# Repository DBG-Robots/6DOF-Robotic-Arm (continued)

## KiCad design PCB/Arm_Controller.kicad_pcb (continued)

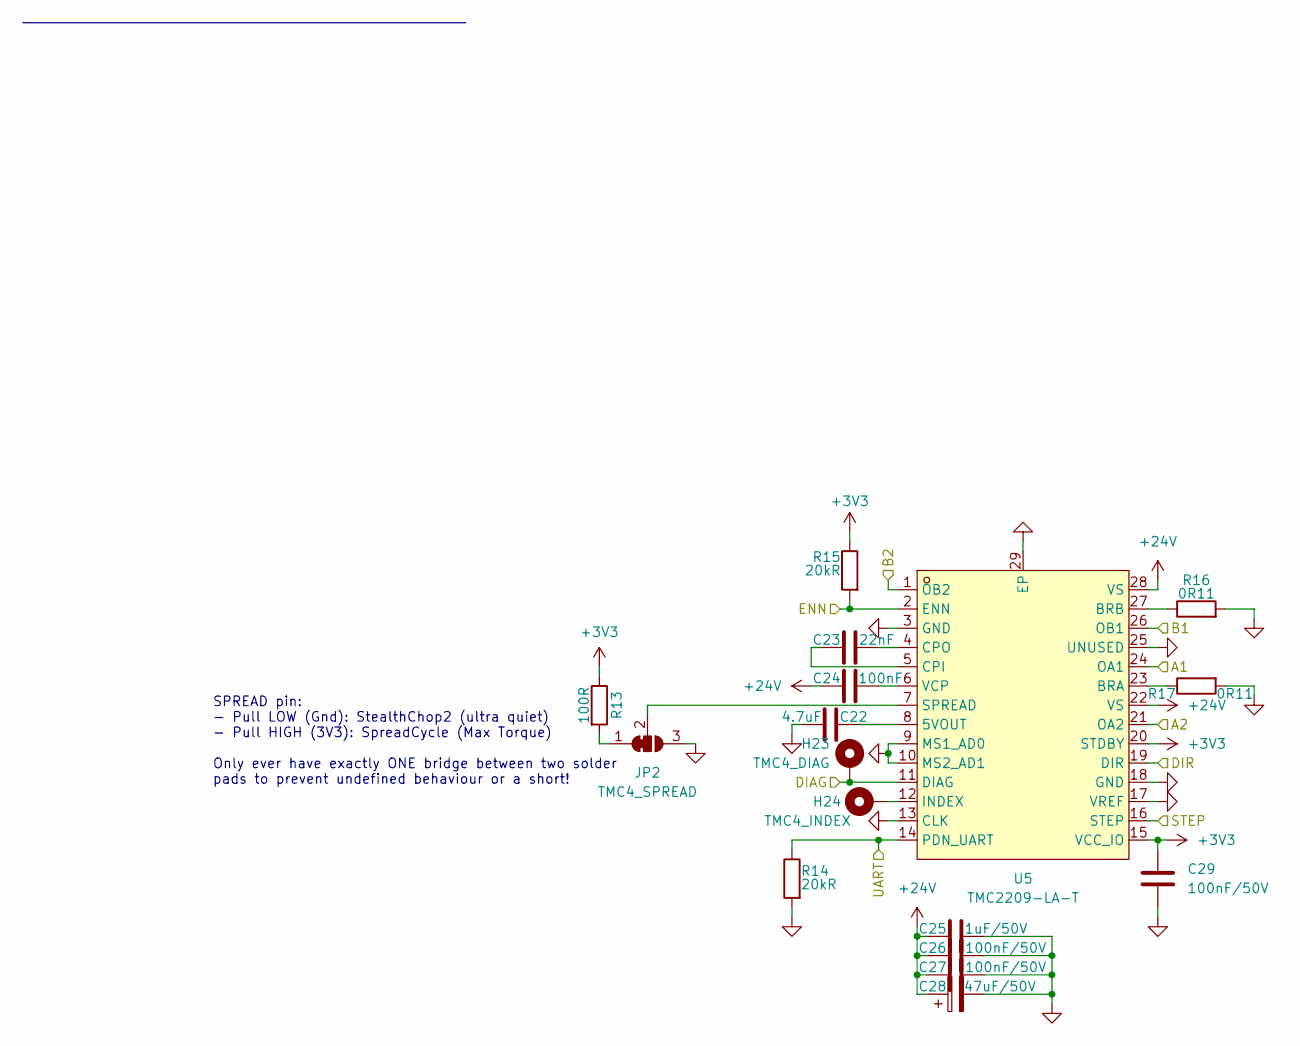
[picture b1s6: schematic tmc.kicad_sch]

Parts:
C22: 4.7uF; C_0805_2012Metric
C23: 22nF; C_0402_1005Metric
C24: 100nF; C_0402_1005Metric
C25: 1uF/50V; C_0603_1608Metric
C26, C27, C29: 100nF/50V; C_0402_1005Metric
C28: 47uF/50V; CP_Elec_8x10.5
H23: TMC4_DIAG; TestPoint_Pad_D1.0mm
H24: TMC4_INDEX; TestPoint_Pad_D1.0mm
JP2: TMC4_SPREAD; SolderJumper-3_P1.3mm_Bridged2Bar12_RoundedPad1.0x1.5mm
R13: 100R; R_0402_1005Metric
R14, R15: 20kR; R_0402_1005Metric
R16, R17: 0R11; R_1206_3216Metric
U5: TMC2209-LA-T; QFN-28_L5.0-W5.0-P0.50-BL-EP; MPN TMC2209-LA-T; LCSC Part C2150710

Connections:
+3V3: C29.1, R13.1, R15.1, U5.15 (VCC_IO), U5.20 (STDBY); also elsewhere on the board
+24V: C24.1, C25.1, C26.1, C27.1, C28.1, U5.22 (VS), U5.28 (VS); also elsewhere on the board
GND: C22.1, C25.2, C26.2, C27.2, C28.2, C29.2, JP2.3 (B), R14.2, R16.2, R17.2, U5.3 (GND), U5.9 (MS1_AD0), U5.10 (MS2_AD1), U5.13 (CLK), U5.17 (VREF), U5.18 (GND), U5.25 (UNUSED), U5.29 (EP); also elsewhere on the board
unnamed: JP2.1 (A), R13.2
unnamed: JP2.2 (C), U5.7 (SPREAD)
unnamed: C22.2, U5.8 (5VOUT)
unnamed: R17.1, U5.23 (BRA)
unnamed: R16.1, U5.27 (BRB)
unnamed: C23.1, U5.5 (CPI)
unnamed: C23.2, U5.4 (CPO)
unnamed: H24.1 (1_1), U5.12 (INDEX)
unnamed: C24.2, U5.6 (VCP)
TMC1_A1: U5.24 (OA1); also elsewhere on the board
TMC1_A2: U5.21 (OA2); also elsewhere on the board
TMC1_B1: U5.26 (OB1); also elsewhere on the board
TMC1_B2: U5.1 (OB2); also elsewhere on the board
TMC1_DIAG: H23.1 (1_1), U5.11 (DIAG); also elsewhere on the board
TMC1_DIR: U5.19 (DIR); also elsewhere on the board
TMC1_STEP: U5.16 (STEP); also elsewhere on the board
TMC_A_ENN: R15.2, U5.2 (ENN); also elsewhere on the board
USART1: R14.1, U5.14 (PDN_UART); also elsewhere on the board

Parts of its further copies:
C30, C38, C46, C54, C62: 4.7uF; C_0805_2012Metric
C31, C39, C47, C55, C63: 22nF; C_0402_1005Metric
C32, C40, C48, C56, C64: 100nF; C_0402_1005Metric
C33, C41, C49, C57, C65: 1uF/50V; C_0603_1608Metric
C34, C35, C37, C42, C43, C45, C50, C51, C53, C58, C59, C61, C66, C67, C69: 100nF/50V; C_0402_1005Metric
C36, C44, C52, C60, C68: 47uF/50V; CP_Elec_8x10.5
H25, H27, H29, H31, H33: TMC4_DIAG; TestPoint_Pad_D1.0mm
H26, H28, H30, H32, H34: TMC4_INDEX; TestPoint_Pad_D1.0mm
JP3, JP4, JP5, JP6, JP7: TMC4_SPREAD; SolderJumper-3_P1.3mm_Bridged2Bar12_RoundedPad1.0x1.5mm
R18, R23, R28, R33, R38: 100R; R_0402_1005Metric
R19, R20, R24, R25, R29, R30, R34, R35, R39, R40: 20kR; R_0402_1005Metric
R21, R22, R26, R27, R31, R32, R36, R37, R41, R42: 0R11; R_1206_3216Metric
U6, U7, U8, U9, U10: TMC2209-LA-T; QFN-28_L5.0-W5.0-P0.50-BL-EP; MPN TMC2209-LA-T; LCSC Part C2150710

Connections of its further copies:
+3V3: C37.1, C45.1, C53.1, C61.1, C69.1, R18.1, R20.1, R23.1, R25.1, R28.1, R30.1, R33.1, R35.1, R38.1, R40.1, U6.15 (VCC_IO), U6.20 (STDBY), U7.15 (VCC_IO), U7.20 (STDBY), U8.15 (VCC_IO), U8.20 (STDBY), U9.15 (VCC_IO), U9.20 (STDBY), U10.15 (VCC_IO), U10.20 (STDBY); also elsewhere on the board
+24V: C32.1, C33.1, C34.1, C35.1, C36.1, C40.1, C41.1, C42.1, C43.1, C44.1, C48.1, C49.1, C50.1, C51.1, C52.1, C56.1, C57.1, C58.1, C59.1, C60.1, C64.1, C65.1, C66.1, C67.1, C68.1, U6.22 (VS), U6.28 (VS), U7.22 (VS), U7.28 (VS), U8.22 (VS), U8.28 (VS), U9.22 (VS), U9.28 (VS), U10.22 (VS), U10.28 (VS); also elsewhere on the board
GND: C30.1, C33.2, C34.2, C35.2, C36.2, C37.2, C38.1, C41.2, C42.2, C43.2, C44.2, C45.2, C46.1, C49.2, C50.2, C51.2, C52.2, C53.2, C54.1, C57.2, C58.2, C59.2, C60.2, C61.2, C62.1, C65.2, C66.2, C67.2, C68.2, C69.2, JP3.3 (B), JP4.3 (B), JP5.3 (B), JP6.3 (B), JP7.3 (B), R19.2, R21.2, R22.2, R24.2, R26.2, R27.2, R29.2, R31.2, R32.2, R34.2, R36.2, R37.2, R39.2, R41.2, R42.2, U6.3 (GND), U6.9 (MS1_AD0), U6.10 (MS2_AD1), U6.13 (CLK), U6.17 (VREF), U6.18 (GND), U6.25 (UNUSED), U6.29 (EP), U7.3 (GND), U7.9 (MS1_AD0), U7.10 (MS2_AD1), U7.13 (CLK), U7.17 (VREF), U7.18 (GND), U7.25 (UNUSED), U7.29 (EP), U8.3 (GND), U8.9 (MS1_AD0), U8.10 (MS2_AD1), U8.13 (CLK), U8.17 (VREF), U8.18 (GND), U8.25 (UNUSED), U8.29 (EP), U9.3 (GND), U9.9 (MS1_AD0), U9.10 (MS2_AD1), U9.13 (CLK), U9.17 (VREF), U9.18 (GND), U9.25 (UNUSED), U9.29 (EP), U10.3 (GND), U10.9 (MS1_AD0), U10.10 (MS2_AD1), U10.13 (CLK), U10.17 (VREF), U10.18 (GND), U10.25 (UNUSED), U10.29 (EP); also elsewhere on the board
unnamed: JP3.1 (A), R18.2
unnamed: JP3.2 (C), U6.7 (SPREAD)
unnamed: JP4.1 (A), R23.2
unnamed: JP4.2 (C), U7.7 (SPREAD)
unnamed: JP5.1 (A), R28.2
unnamed: JP5.2 (C), U8.7 (SPREAD)
unnamed: JP6.1 (A), R33.2
unnamed: JP6.2 (C), U9.7 (SPREAD)
unnamed: JP7.1 (A), R38.2
unnamed: JP7.2 (C), U10.7 (SPREAD)
unnamed: C30.2, U6.8 (5VOUT)
unnamed: R22.1, U6.23 (BRA)
unnamed: R21.1, U6.27 (BRB)
unnamed: C31.1, U6.5 (CPI)
unnamed: C31.2, U6.4 (CPO)
unnamed: H26.1 (1_1), U6.12 (INDEX)
unnamed: C32.2, U6.6 (VCP)
unnamed: C38.2, U7.8 (5VOUT)
unnamed: R27.1, U7.23 (BRA)
unnamed: R26.1, U7.27 (BRB)
unnamed: C39.1, U7.5 (CPI)
unnamed: C39.2, U7.4 (CPO)
unnamed: H28.1 (1_1), U7.12 (INDEX)
unnamed: C40.2, U7.6 (VCP)
unnamed: C46.2, U8.8 (5VOUT)
unnamed: R32.1, U8.23 (BRA)
unnamed: R31.1, U8.27 (BRB)
unnamed: C47.1, U8.5 (CPI)
unnamed: C47.2, U8.4 (CPO)
unnamed: H30.1 (1_1), U8.12 (INDEX)
unnamed: C48.2, U8.6 (VCP)
unnamed: C54.2, U9.8 (5VOUT)
unnamed: R37.1, U9.23 (BRA)
unnamed: R36.1, U9.27 (BRB)
unnamed: C55.1, U9.5 (CPI)
unnamed: C55.2, U9.4 (CPO)
unnamed: H32.1 (1_1), U9.12 (INDEX)
unnamed: C56.2, U9.6 (VCP)
unnamed: C62.2, U10.8 (5VOUT)
unnamed: R42.1, U10.23 (BRA)
unnamed: R41.1, U10.27 (BRB)
unnamed: C63.1, U10.5 (CPI)
unnamed: C63.2, U10.4 (CPO)
unnamed: H34.1 (1_1), U10.12 (INDEX)
unnamed: C64.2, U10.6 (VCP)
TMC2_A1: U6.24 (OA1); also elsewhere on the board
TMC2_A2: U6.21 (OA2); also elsewhere on the board
TMC2_B1: U6.26 (OB1); also elsewhere on the board
TMC2_B2: U6.1 (OB2); also elsewhere on the board
TMC2_DIAG: H25.1 (1_1), H31.1 (1_1), U6.11 (DIAG), U9.11 (DIAG); also elsewhere on the board
TMC2_DIR: U6.19 (DIR), U9.19 (DIR); also elsewhere on the board
TMC2_STEP: U6.16 (STEP), U9.16 (STEP); also elsewhere on the board
TMC3_A1: U7.24 (OA1); also elsewhere on the board
TMC3_A2: U7.21 (OA2); also elsewhere on the board
TMC3_B1: U7.26 (OB1); also elsewhere on the board
TMC3_B2: U7.1 (OB2); also elsewhere on the board
TMC3_DIAG: H27.1 (1_1), U7.11 (DIAG); also elsewhere on the board
TMC3_DIR: U7.19 (DIR); also elsewhere on the board
TMC3_STEP: U7.16 (STEP); also elsewhere on the board
TMC4_A1: U8.24 (OA1); also elsewhere on the board
TMC4_A2: U8.21 (OA2); also elsewhere on the board
TMC4_B1: U8.26 (OB1); also elsewhere on the board
TMC4_B2: U8.1 (OB2); also elsewhere on the board
TMC4_DIAG: H29.1 (1_1), U8.11 (DIAG); also elsewhere on the board
TMC4_DIR: U8.19 (DIR); also elsewhere on the board
TMC4_STEP: U8.16 (STEP); also elsewhere on the board
TMC5_A1: U9.24 (OA1); also elsewhere on the board
TMC5_A2: U9.21 (OA2); also elsewhere on the board
TMC5_B1: U9.26 (OB1); also elsewhere on the board
TMC5_B2: U9.1 (OB2); also elsewhere on the board
TMC6_A1: U10.24 (OA1); also elsewhere on the board
TMC6_A2: U10.21 (OA2); also elsewhere on the board
TMC6_B1: U10.26 (OB1); also elsewhere on the board
TMC6_B2: U10.1 (OB2); also elsewhere on the board
TMC6_DIAG: H33.1 (1_1), U10.11 (DIAG); also elsewhere on the board
TMC6_DIR: U10.19 (DIR); also elsewhere on the board
TMC6_STEP: U10.16 (STEP); also elsewhere on the board
TMC_A_ENN: R20.2, R25.2, U6.2 (ENN), U7.2 (ENN); also elsewhere on the board
TMC_B_ENN: R30.2, R35.2, R40.2, U8.2 (ENN), U9.2 (ENN), U10.2 (ENN); also elsewhere on the board
USART1: R19.1, R24.1, U6.14 (PDN_UART), U7.14 (PDN_UART); also elsewhere on the board
USART2: R29.1, R34.1, R39.1, U8.14 (PDN_UART), U9.14 (PDN_UART), U10.14 (PDN_UART); also elsewhere on the board

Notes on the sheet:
SPREAD pin: - Pull LOW (Gnd): StealthChop2 (ultra quiet) - Pull HIGH (3V3): SpreadCycle (Max Torque) Only ever have exactly ONE bridge between two solder pads to prevent undefined behaviour or a short!

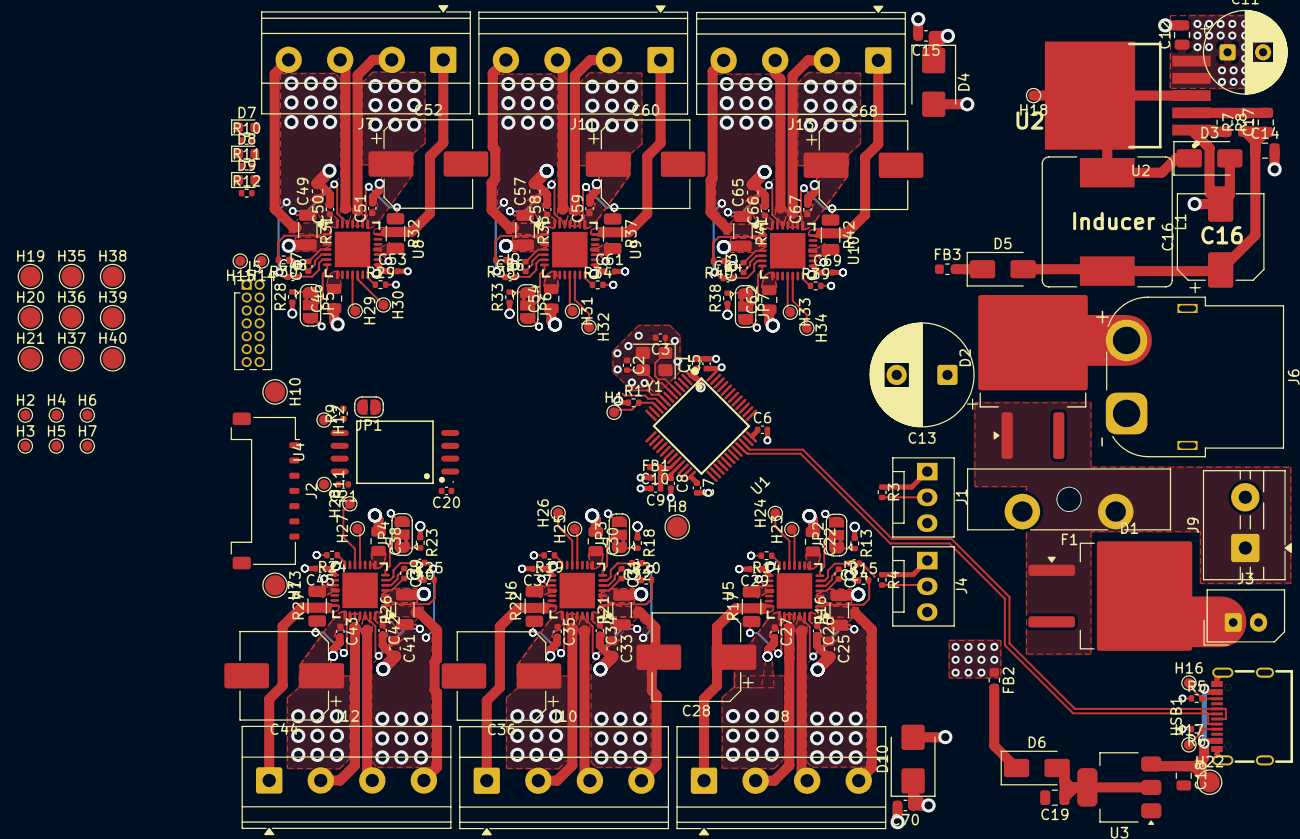
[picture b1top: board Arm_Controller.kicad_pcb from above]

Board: 4 copper layers, 196 parts (0 on the bottom side), 136 nets.

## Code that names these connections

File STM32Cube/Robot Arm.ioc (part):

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Mcu.Name=STM32G431C(6-8-B)Tx
Mcu.Package=LQFP48
Mcu.UserName=STM32G431CBTx
PA0.GPIOParameters=GPIO_Label
PA0.GPIO_Label=TMC1_STEP
PA0.Signal=S_TIM2_CH1
PA1.GPIOParameters=GPIO_Label
PA1.GPIO_Label=TMC2_STEP
PA1.Signal=S_TIM2_CH2
PA10.Signal=GPIO_Output
PA11.Mode=Device
PA11.Signal=USB_DM
PA12.Mode=Device
PA12.Signal=USB_DP
PA13.Mode=Serial_Wire
PA13.Signal=SYS_JTMS-SWDIO
PA14.Mode=Serial_Wire
PA14.Signal=SYS_JTCK-SWCLK
PA15.Signal=GPIO_Output
PA3.GPIOParameters=GPIO_Label
PA3.GPIO_Label=TMC1_DIR
PA3.Signal=GPIO_Output
PA4.GPIOParameters=GPIO_Label
PA4.GPIO_Label=TMC1_DIR
PA4.Signal=GPIO_Output
PA5.GPIOParameters=GPIO_Label
PA5.GPIO_Label=TMC3_DIR
PA5.Signal=GPIO_Output
PA6.GPIOParameters=GPIO_Label
PA6.GPIO_Label=TMC3_STEP
PA6.Signal=S_TIM3_CH1
PA7.GPIOParameters=GPIO_Label
PA7.GPIO_Label=TMC4_STEP
PA7.Signal=S_TIM3_CH2
PA8.GPIOParameters=GPIO_Label
PA8.GPIO_Label=LED_ACT
PA8.Signal=GPIO_Output
PA9.GPIOParameters=GPIO_ModeDefaultOD
PA9.GPIO_ModeDefaultOD=GPIO_MODE_AF_OD
PA9.Mode=Half_duplex(single_wire_mode)
PA9.Signal=USART1_TX
PB0.GPIOParameters=GPIO_Label
PB0.GPIO_Label=TMC5_STEP
PB0.Signal=S_TIM3_CH3
PB1.GPIOParameters=GPIO_Label
PB1.GPIO_Label=TMC6_STEP
PB1.Signal=S_TIM3_CH4
PB10.GPIOParameters=GPIO_Label
PB10.GPIO_Label=TMC1_DIAG
PB10.Signal=GPIO_Input
PB11.GPIOParameters=GPIO_Label
PB11.GPIO_Label=TMC2_DIAG
PB11.Signal=GPIO_Input
PB12.GPIOParameters=GPIO_Label
PB12.GPIO_Label=TMC3_DIAG
PB12.Signal=GPIO_Input
PB13.GPIOParameters=GPIO_Label
PB13.GPIO_Label=TMC4_DIAG
PB13.Signal=GPIO_Input
PB14.GPIOParameters=GPIO_Label
PB14.GPIO_Label=TMC5_DIAG
PB14.Signal=GPIO_Input
PB15.GPIOParameters=GPIO_Label
PB15.GPIO_Label=TMC5_DIAG
PB15.Signal=GPIO_Input
PB3.Mode=Half_duplex(single_wire_mode)
PB3.Signal=USART2_TX
PB4.GPIOParameters=GPIO_Label
PB4.GPIO_Label=TMC4_DIR
PB4.Signal=GPIO_Output
PB5.GPIOParameters=GPIO_Label
PB5.GPIO_Label=TMC5_DIR
PB5.Signal=GPIO_Output
PB6.GPIOParameters=GPIO_Label
PB6.GPIO_Label=TMC6_DIR
PB6.Signal=GPIO_Output
PB8-BOOT0.Mode=FDCAN_Activate
PB8-BOOT0.Signal=FDCAN1_RX
PB9.Mode=FDCAN_Activate
PB9.Signal=FDCAN1_TX
PC13.GPIOParameters=GPIO_Label
PC13.GPIO_Label=LED_STAT
PC13.Signal=GPIO_Output
PF0-OSC_IN.Mode=HSE-External-Oscillator
PF0-OSC_IN.Signal=RCC_OSC_IN
PF1-OSC_OUT.Mode=HSE-External-Oscillator
PF1-OSC_OUT.Signal=RCC_OSC_OUT
RCC.HSE_VALUE=8000000
RCC.SYSCLKFreq_VALUE=170000000
RCC.SYSCLKSource=RCC_SYSCLKSOURCE_PLLCLK
board=custom

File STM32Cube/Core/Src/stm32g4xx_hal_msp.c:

/* USER CODE BEGIN Header */
/**
  ******************************************************************************
  * @file         stm32g4xx_hal_msp.c
  * @brief        This file provides code for the MSP Initialization
  *               and de-Initialization codes.
  ******************************************************************************
  * @attention
  *
  * Copyright (c) 2026 STMicroelectronics.
  * All rights reserved.
  *
  * This software is licensed under terms that can be found in the LICENSE file
  * in the root directory of this software component.
  * If no LICENSE file comes with this software, it is provided AS-IS.
  *
  ******************************************************************************
  */
/* USER CODE END Header */

/* Includes ------------------------------------------------------------------*/
#include "main.h"
/* USER CODE BEGIN Includes */

/* USER CODE END Includes */

/* Private typedef -----------------------------------------------------------*/
/* USER CODE BEGIN TD */

/* USER CODE END TD */

/* Private define ------------------------------------------------------------*/
/* USER CODE BEGIN Define */

/* USER CODE END Define */

/* Private macro -------------------------------------------------------------*/
/* USER CODE BEGIN Macro */

/* USER CODE END Macro */

/* Private variables ---------------------------------------------------------*/
/* USER CODE BEGIN PV */

/* USER CODE END PV */

/* Private function prototypes -----------------------------------------------*/
/* USER CODE BEGIN PFP */

/* USER CODE END PFP */

/* External functions --------------------------------------------------------*/
/* USER CODE BEGIN ExternalFunctions */

/* USER CODE END ExternalFunctions */

/* USER CODE BEGIN 0 */

/* USER CODE END 0 */
/**
  * Initializes the Global MSP.
  */
void HAL_MspInit(void)
{

  /* USER CODE BEGIN MspInit 0 */

  /* USER CODE END MspInit 0 */

  __HAL_RCC_SYSCFG_CLK_ENABLE();
  __HAL_RCC_PWR_CLK_ENABLE();

  /* System interrupt init*/

  /** Disable the internal Pull-Up in Dead Battery pins of UCPD peripheral
  */
  HAL_PWREx_DisableUCPDDeadBattery();

  /* USER CODE BEGIN MspInit 1 */

  /* USER CODE END MspInit 1 */
}

/**
  * @brief FDCAN MSP Initialization
  * This function configures the hardware resources used in this example
  * @param hfdcan: FDCAN handle pointer
  * @retval None
  */
void HAL_FDCAN_MspInit(FDCAN_HandleTypeDef* hfdcan)
{
  GPIO_InitTypeDef GPIO_InitStruct = {0};
  RCC_PeriphCLKInitTypeDef PeriphClkInit = {0};
  if(hfdcan->Instance==FDCAN1)
  {
    /* USER CODE BEGIN FDCAN1_MspInit 0 */

    /* USER CODE END FDCAN1_MspInit 0 */

  /** Initializes the peripherals clocks
  */
    PeriphClkInit.PeriphClockSelection = RCC_PERIPHCLK_FDCAN;
    PeriphClkInit.FdcanClockSelection = RCC_FDCANCLKSOURCE_PCLK1;
    if (HAL_RCCEx_PeriphCLKConfig(&PeriphClkInit) != HAL_OK)
    {
      Error_Handler();
    }

    /* Peripheral clock enable */
    __HAL_RCC_FDCAN_CLK_ENABLE();

    __HAL_RCC_GPIOB_CLK_ENABLE();
    /**FDCAN1 GPIO Configuration
    PB8-BOOT0     ------> FDCAN1_RX
    PB9     ------> FDCAN1_TX
    */
    GPIO_InitStruct.Pin = GPIO_PIN_8|GPIO_PIN_9;
    GPIO_InitStruct.Mode = GPIO_MODE_AF_PP;
    GPIO_InitStruct.Pull = GPIO_NOPULL;
    GPIO_InitStruct.Speed = GPIO_SPEED_FREQ_LOW;
    GPIO_InitStruct.Alternate = GPIO_AF9_FDCAN1;
    HAL_GPIO_Init(GPIOB, &GPIO_InitStruct);

    /* USER CODE BEGIN FDCAN1_MspInit 1 */

    /* USER CODE END FDCAN1_MspInit 1 */

  }

}

/**
  * @brief FDCAN MSP De-Initialization
  * This function freeze the hardware resources used in this example
  * @param hfdcan: FDCAN handle pointer
  * @retval None
  */
void HAL_FDCAN_MspDeInit(FDCAN_HandleTypeDef* hfdcan)
{
  if(hfdcan->Instance==FDCAN1)
  {
    /* USER CODE BEGIN FDCAN1_MspDeInit 0 */

    /* USER CODE END FDCAN1_MspDeInit 0 */
    /* Peripheral clock disable */
    __HAL_RCC_FDCAN_CLK_DISABLE();

    /**FDCAN1 GPIO Configuration
    PB8-BOOT0     ------> FDCAN1_RX
    PB9     ------> FDCAN1_TX
    */
    HAL_GPIO_DeInit(GPIOB, GPIO_PIN_8|GPIO_PIN_9);

    /* USER CODE BEGIN FDCAN1_MspDeInit 1 */

    /* USER CODE END FDCAN1_MspDeInit 1 */
  }

}

/**
  * @brief UART MSP Initialization
  * This function configures the hardware resources used in this example
  * @param huart: UART handle pointer
  * @retval None
  */
void HAL_UART_MspInit(UART_HandleTypeDef* huart)
{
  GPIO_InitTypeDef GPIO_InitStruct = {0};
  RCC_PeriphCLKInitTypeDef PeriphClkInit = {0};
  if(huart->Instance==USART1)
  {
    /* USER CODE BEGIN USART1_MspInit 0 */

    /* USER CODE END USART1_MspInit 0 */

  /** Initializes the peripherals clocks
  */
    PeriphClkInit.PeriphClockSelection = RCC_PERIPHCLK_USART1;
    PeriphClkInit.Usart1ClockSelection = RCC_USART1CLKSOURCE_PCLK2;
    if (HAL_RCCEx_PeriphCLKConfig(&PeriphClkInit) != HAL_OK)
    {
      Error_Handler();
    }

    /* Peripheral clock enable */
    __HAL_RCC_USART1_CLK_ENABLE();

    __HAL_RCC_GPIOA_CLK_ENABLE();
    /**USART1 GPIO Configuration
    PA9     ------> USART1_TX
    */
    GPIO_InitStruct.Pin = GPIO_PIN_9;
    GPIO_InitStruct.Mode = GPIO_MODE_AF_OD;
    GPIO_InitStruct.Pull = GPIO_NOPULL;
    GPIO_InitStruct.Speed = GPIO_SPEED_FREQ_LOW;
    GPIO_InitStruct.Alternate = GPIO_AF7_USART1;
    HAL_GPIO_Init(GPIOA, &GPIO_InitStruct);

    /* USART1 interrupt Init */
    HAL_NVIC_SetPriority(USART1_IRQn, 0, 0);
    HAL_NVIC_EnableIRQ(USART1_IRQn);
    /* USER CODE BEGIN USART1_MspInit 1 */

    /* USER CODE END USART1_MspInit 1 */
  }
  else if(huart->Instance==USART2)
  {
    /* USER CODE BEGIN USART2_MspInit 0 */

    /* USER CODE END USART2_MspInit 0 */

  /** Initializes the peripherals clocks
  */
    PeriphClkInit.PeriphClockSelection = RCC_PERIPHCLK_USART2;
    PeriphClkInit.Usart2ClockSelection = RCC_USART2CLKSOURCE_PCLK1;
    if (HAL_RCCEx_PeriphCLKConfig(&PeriphClkInit) != HAL_OK)
    {
      Error_Handler();
    }

    /* Peripheral clock enable */
    __HAL_RCC_USART2_CLK_ENABLE();

    __HAL_RCC_GPIOB_CLK_ENABLE();
    /**USART2 GPIO Configuration
    PB3     ------> USART2_TX
    */
    GPIO_InitStruct.Pin = GPIO_PIN_3;
    GPIO_InitStruct.Mode = GPIO_MODE_AF_OD;
    GPIO_InitStruct.Pull = GPIO_NOPULL;
    GPIO_InitStruct.Speed = GPIO_SPEED_FREQ_LOW;
    GPIO_InitStruct.Alternate = GPIO_AF7_USART2;
    HAL_GPIO_Init(GPIOB, &GPIO_InitStruct);

    /* USER CODE BEGIN USART2_MspInit 1 */

    /* USER CODE END USART2_MspInit 1 */
  }

}

/**
  * @brief UART MSP De-Initialization
  * This function freeze the hardware resources used in this example
  * @param huart: UART handle pointer
  * @retval None
  */
void HAL_UART_MspDeInit(UART_HandleTypeDef* huart)
{
  if(huart->Instance==USART1)
  {
    /* USER CODE BEGIN USART1_MspDeInit 0 */

    /* USER CODE END USART1_MspDeInit 0 */
    /* Peripheral clock disable */
    __HAL_RCC_USART1_CLK_DISABLE();

    /**USART1 GPIO Configuration
    PA9     ------> USART1_TX
    */
    HAL_GPIO_DeInit(GPIOA, GPIO_PIN_9);

    /* USART1 interrupt DeInit */
    HAL_NVIC_DisableIRQ(USART1_IRQn);
    /* USER CODE BEGIN USART1_MspDeInit 1 */

    /* USER CODE END USART1_MspDeInit 1 */
  }
  else if(huart->Instance==USART2)
  {
    /* USER CODE BEGIN USART2_MspDeInit 0 */

    /* USER CODE END USART2_MspDeInit 0 */
    /* Peripheral clock disable */
    __HAL_RCC_USART2_CLK_DISABLE();

    /**USART2 GPIO Configuration
    PB3     ------> USART2_TX
    */
    HAL_GPIO_DeInit(GPIOB, GPIO_PIN_3);

    /* USER CODE BEGIN USART2_MspDeInit 1 */

    /* USER CODE END USART2_MspDeInit 1 */
  }

}

/**
  * @brief PCD MSP Initialization
  * This function configures the hardware resources used in this example
  * @param hpcd: PCD handle pointer
  * @retval None
  */
void HAL_PCD_MspInit(PCD_HandleTypeDef* hpcd)
{
  RCC_PeriphCLKInitTypeDef PeriphClkInit = {0};
  if(hpcd->Instance==USB)
  {
    /* USER CODE BEGIN USB_MspInit 0 */

    /* USER CODE END USB_MspInit 0 */

  /** Initializes the peripherals clocks
  */
    PeriphClkInit.PeriphClockSelection = RCC_PERIPHCLK_USB;
    PeriphClkInit.UsbClockSelection = RCC_USBCLKSOURCE_HSI48;
    if (HAL_RCCEx_PeriphCLKConfig(&PeriphClkInit) != HAL_OK)
    {
      Error_Handler();
    }

    /* Peripheral clock enable */
    __HAL_RCC_USB_CLK_ENABLE();
    /* USER CODE BEGIN USB_MspInit 1 */

    /* USER CODE END USB_MspInit 1 */

  }

}

/**
  * @brief PCD MSP De-Initialization
  * This function freeze the hardware resources used in this example
  * @param hpcd: PCD handle pointer
  * @retval None
  */
void HAL_PCD_MspDeInit(PCD_HandleTypeDef* hpcd)
{
  if(hpcd->Instance==USB)
  {
    /* USER CODE BEGIN USB_MspDeInit 0 */

    /* USER CODE END USB_MspDeInit 0 */
    /* Peripheral clock disable */
    __HAL_RCC_USB_CLK_DISABLE();
    /* USER CODE BEGIN USB_MspDeInit 1 */

    /* USER CODE END USB_MspDeInit 1 */
  }

}

/* USER CODE BEGIN 1 */

/* USER CODE END 1 */

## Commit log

2026-05-27 Added STM32Cube Project
2026-05-27 Revise README for 6DOF Robotic Arm project
    Updated project title and added detailed project overview, status, repository structure, hardware overview, pin assignments, and known issues.
2026-05-27 Remove project name from README title
2026-05-27 Minor Schematic tweaks like - Adding pull up resistors to the spare GPIO pins - Renaming some Global Labels - Labeling all the pins on the STM32 correctly
2026-05-27 Improved Protection and Board Testability - Added power rail protection and decoupling for stepper motor noise environment - Added TVS, bulk caps and fuse upgrade on 24V rail - Added test pads for br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
2026-05-27 Enhance clarity and detail in README.md
    Updated README.md to improve clarity and detail in various sections, including motor output connections, power inputs, and test points.
2026-05-28 PCB Layout: Initial TMC2209 driver cluster layout
    - Defined netclasses for 24V, Stepper Motor, 3V3, 5V and Signal
    - Decided on 4-layer stackup: Signal / GND / Power / Signal
    - Routed high current motor output traces with tapered zone fills
    - Placed and routed VS decoupling caps (100nF, 1uF, 47uF electrolytic)
    - Routed sense resistors with dedicated GND vias per resistor
    - Routed BRA/BRB via bottom layer with perpendicular crossing under motor traces
2026-05-28 Started laying out the PCB - Decided for a square-shaped board - Split Motor Controllers on top and bottom - Split Power Plane (+3V3 on logic side, +24V on motor side) - Roughly layed out the board e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
2026-05-30 Continued PCB Development - Routed MCU decoupeling and Isolated Crystal - Routed LDO Buck converter (VBUS (+5V) -> +3V3) - Routed Buck Converter (+24V -> +3V3) needs review (U2-pin1-GND) - Started Ro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
